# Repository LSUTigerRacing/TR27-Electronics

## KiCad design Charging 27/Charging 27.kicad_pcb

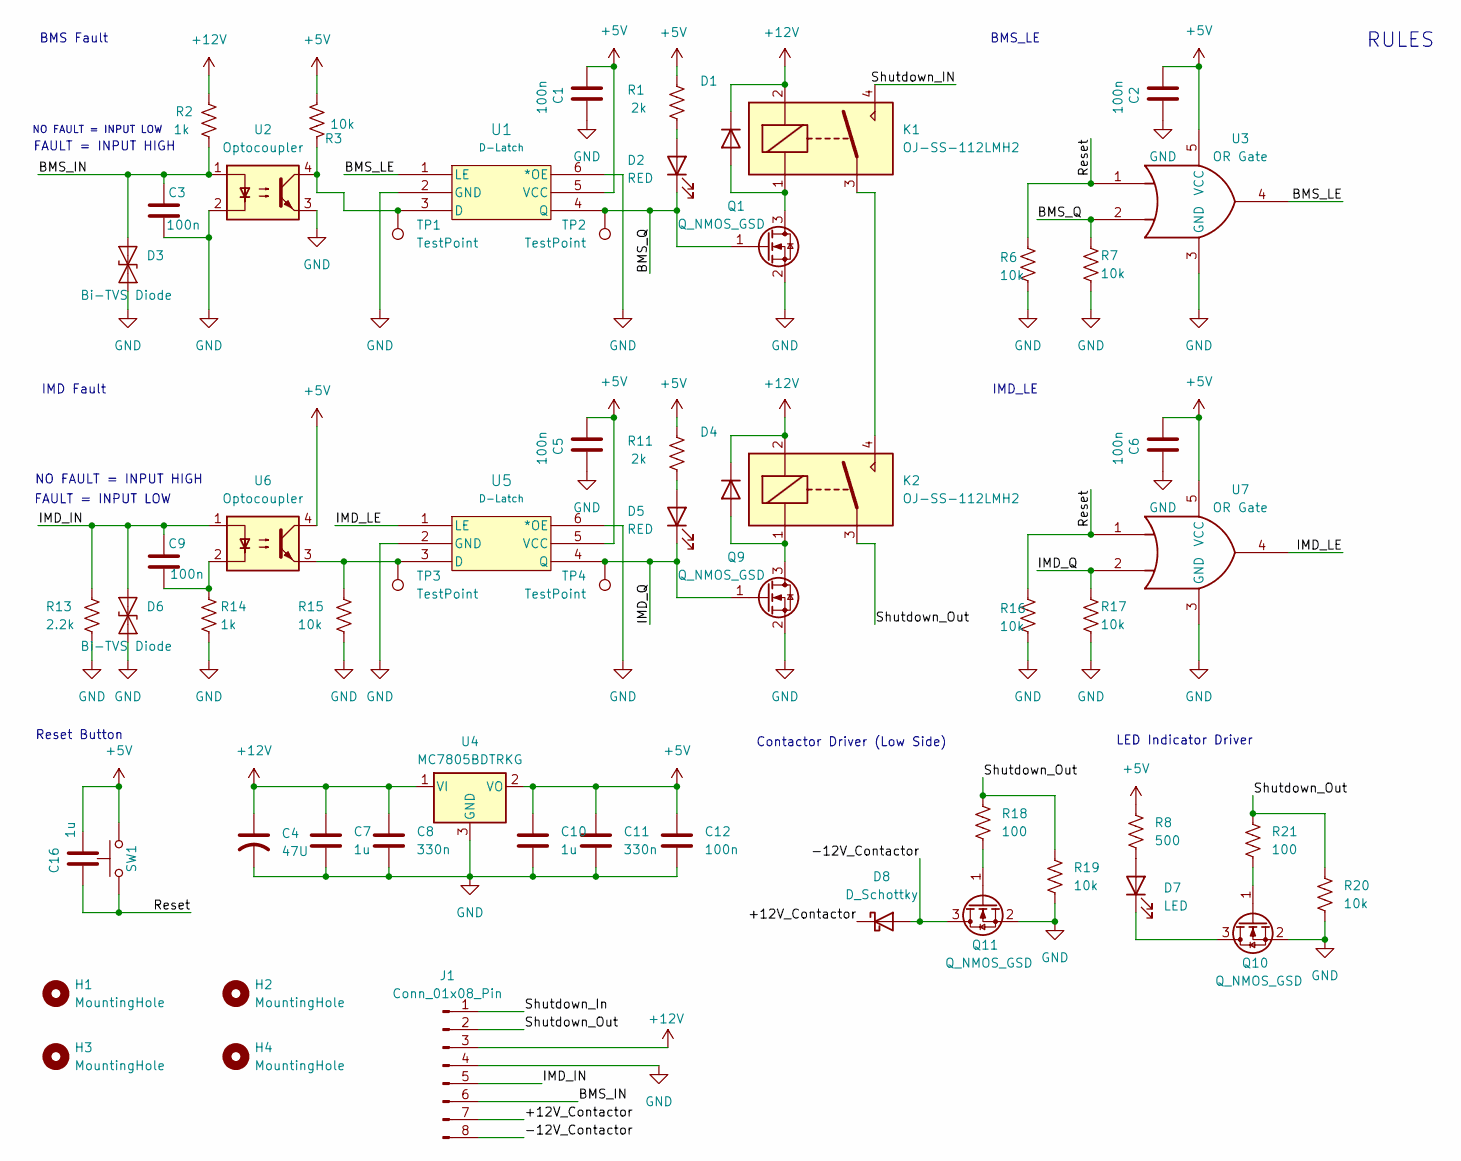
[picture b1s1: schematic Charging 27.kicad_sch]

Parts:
C1, C2, C5, C6: 100n; C_0603_1608Metric; Mouser# 603-AC0603KR9BB104; JLC# C1591
C3, C9: 100n; C_0603_1608Metric; Mouser# 603-AC0603KR9BB104; JLC# C133086
C4: 47U; CP_Elec_6.3x5.4; JLC# C2836440
C7, C10: 1u; C_0603_1608Metric; Mouser# 603-CC603KRX7R9BB105
C8, C11: 330n; C_0603_1608Metric; Mouser# 603-CC603KRX7R6BB334
C12: 100n; C_0603_1608Metric; Mouser# AC0603KRX7R9BB104
C16: 1u; C_0603_1608Metric; Mouser# 603-AC0603KR9BB104; JLC# C1591
D1, D4: D_SOD-323; Mouser# N/A; Digikey# 5399-1N4007WSCT-ND
D2, D5: RED; LED_0805_2012Metric_Pad1.15x1.40mm_HandSolder; Digikey# 475-LSR976-NR-1CT-ND
D3, D6: Bi-TVS Diode; D_SOD-523; Mouser# 750-CPDUR12V-HF; JLC# C2443698
D7: LED; D_1206_3216Metric_Pad1.42x1.75mm_HandSolder; MOUSER 645-598-8260-107F
D8: D_Schottky; D_SOD-323_HandSoldering; MOUSER 78-BAS170WS-HE3_A-08
H1, H2, H3, H4: MountingHole; MountingHole_3.2mm_M3_DIN965_Pad
J1: Conn_01x08_Pin; CONN_SD-43650-002_08_MOL
K1, K2: OJ-SS-112LMH2; OJSS112LMH2; Mouser# 655-OJ-SS-112LMH2
Q1, Q9, Q10, Q11: Q_NMOS_GSD; SOT-23; Mouser# 637-MMFTN6001; JLC# C151421
R1, R11: 2k; R_0805_2012Metric; Mouser# 603-RC0805FR-072KL; JLC# C137097
R2, R14: 1k; R_0805_2012Metric; JLC# C137088
R3, R6, R7, R15, R16, R17: 10k; R_0805_2012Metric; JLC# C137088
R8: 500; R_0603_1608Metric; Mouser# 603-RT0603BRC07500RL
R13: 2.2k; R_1206_3216Metric; Mouser# 660-SG73P2BTTD2201F; JLC# C137088
R18, R21: 100; R_0805_2012Metric; Mouser# 603-AA0805FR-13100RL
R19, R20: 10k; R_0805_2012Metric; Mouser# 603-RC1210JR-0710KL
SW1: SW_Omron_B3FS; SW_SPST_Omron_B3FS-100xP; Mouser# 653-B3FS-1000P; JLC# C271750
TP1, TP2, TP3, TP4: TestPoint; TestPoint_Pad_1.0x1.0mm
U1, U5: D-Latch; SOT-363_SC-70-6; Digikey# 296-18775-1-ND
U2, U6: Optocoupler; SSOP-4_VOS617A_VIS; Digikey# VOS617A-3TTR-ND
U3, U7: OR Gate; SOT-353_SC-70-5; Mouser# 595-SN74LVC1G32DCKR
U4: MC7805BDTRKG; TO-252-3_TabPin2

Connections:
+5V: C1.1, C2.1, C5.1, C6.1, C10.1, C11.1, C12.1, C16.1, R1.2, R3.1, R8.1, R11.2, SW1.2, U1.5 (VCC), U3.5 (VCC), U4.2 (VO), U5.5 (VCC), U6.4, U7.5 (VCC)
+12V: C4.1, C7.1, C8.1, D1.1 (K), D4.1 (K), J1.3, K1.2, K2.2, R2.2, U4.1 (VI)
/+12V_Contactor: D8.1 (K), J1.7
/-12V_Contactor: D8.2 (A), J1.8, Q11.3 (D)
/BMS_IN: C3.1, D3.2 (A2), J1.6, R2.1, U2.1
/BMS_LE: U1.1 (LE), U3.4
/BMS_Q: D2.1 (K), Q1.1 (G), R7.2, TP2.1 (1_1), U1.4 (Q), U3.2
/IMD_IN: C9.1, D6.2 (A2), J1.5, R13.2, U6.1
/IMD_LE: U5.1 (LE), U7.4
/IMD_Q: D5.1 (K), Q9.1 (G), R17.2, TP4.1 (1_1), U5.4 (Q), U7.2
/Reset: C16.2, R6.2, R16.2, SW1.1, U3.1, U7.1
/Shutdown_IN: K1.4
/Shutdown_In: J1.1
/Shutdown_Out: J1.2, K2.3, R18.1, R19.1, R20.1, R21.1
GND: C1.2, C2.2, C3.2, C4.2, C5.2, C6.2, C7.2, C8.2, C10.2, C11.2, C12.2, D3.1 (A1), D6.1 (A1), J1.4, Q1.2 (S), Q9.2 (S), Q10.2 (S), Q11.2 (S), R6.1, R7.1, R13.1, R14.1, R15.1, R16.1, R17.1, R19.2, R20.2, U1.2 (GND), U1.6 (*OE), U2.2, U2.3, U3.3 (GND), U4.3 (GND), U5.2 (GND), U5.6 (*OE), U7.3 (GND)
unnamed: C9.2, R14.2, U6.2
unnamed: D1.2 (A), K1.1, Q1.3 (D)
unnamed: D2.2 (A), R1.1
unnamed: D4.2 (A), K2.1, Q9.3 (D)
unnamed: D5.2 (A), R11.1
unnamed: D7.2 (A), R8.2
unnamed: D7.1 (K), Q10.3 (D)
unnamed: K1.3, K2.4
unnamed: Q10.1 (G), R21.2
unnamed: Q11.1 (G), R18.2
unnamed: R3.2, TP1.1 (1_1), U1.3 (D), U2.4
unnamed: R15.2, TP3.1 (1_1), U5.3 (D), U6.3

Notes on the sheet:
BMS Fault
IMD_LE
Reset Button
Contactor Driver (Low Side)
LED Indicator Driver
NO FAULT = INPUT LOW
BMS_LE
FAULT = INPUT LOW
NO FAULT = INPUT HIGH
IMD Fault
RULES
FAULT = INPUT HIGH

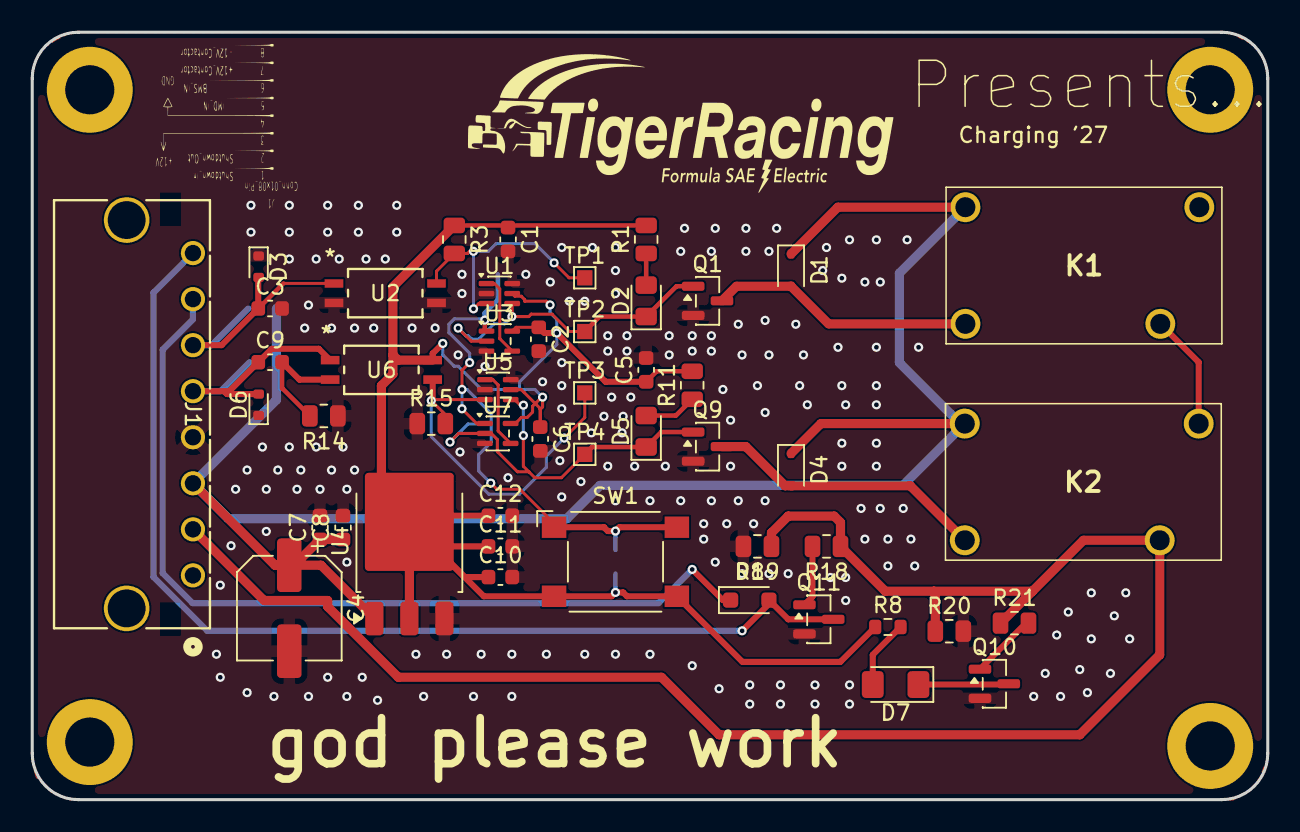
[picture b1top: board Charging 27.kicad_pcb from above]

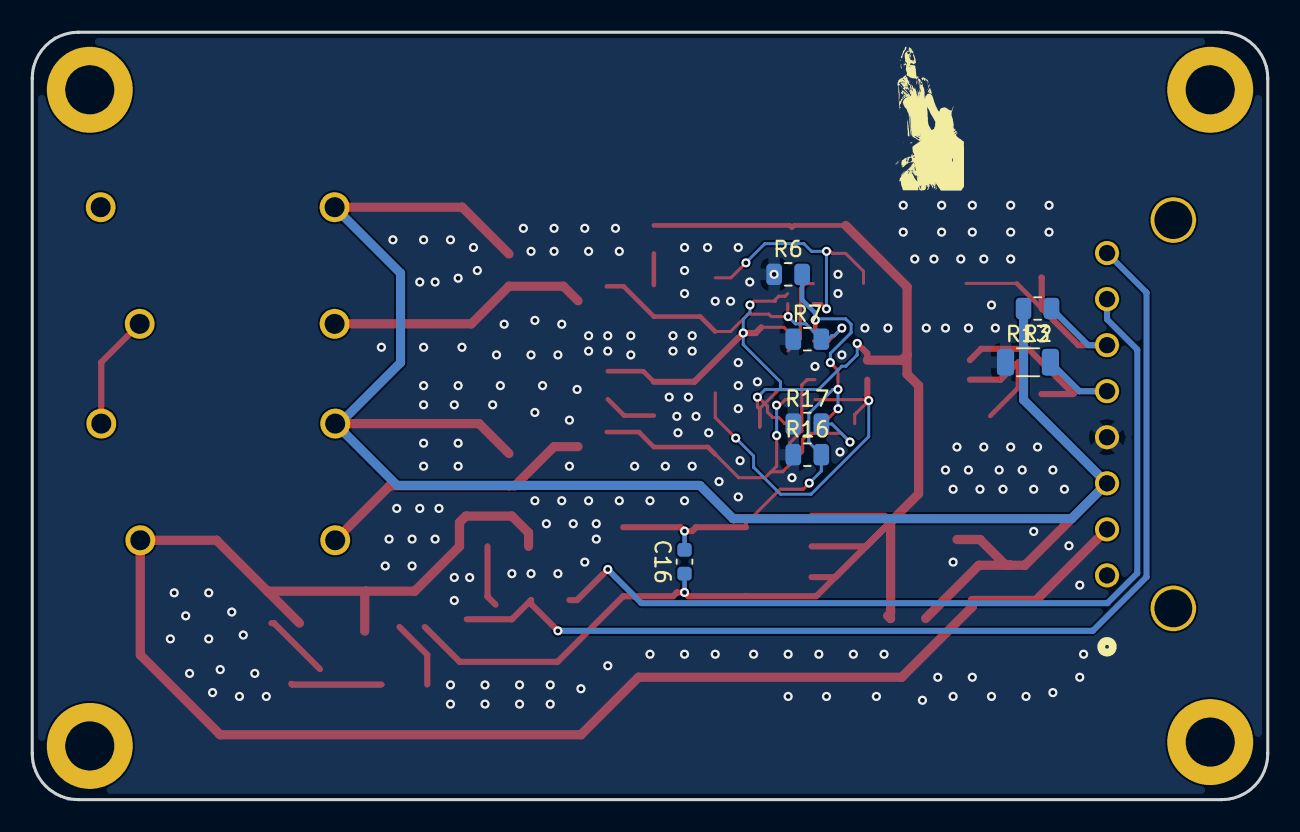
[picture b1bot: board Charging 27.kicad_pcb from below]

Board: 2 copper layers, 80.5 x 50.0 mm, 60 parts (7 on the bottom side), 25 nets.

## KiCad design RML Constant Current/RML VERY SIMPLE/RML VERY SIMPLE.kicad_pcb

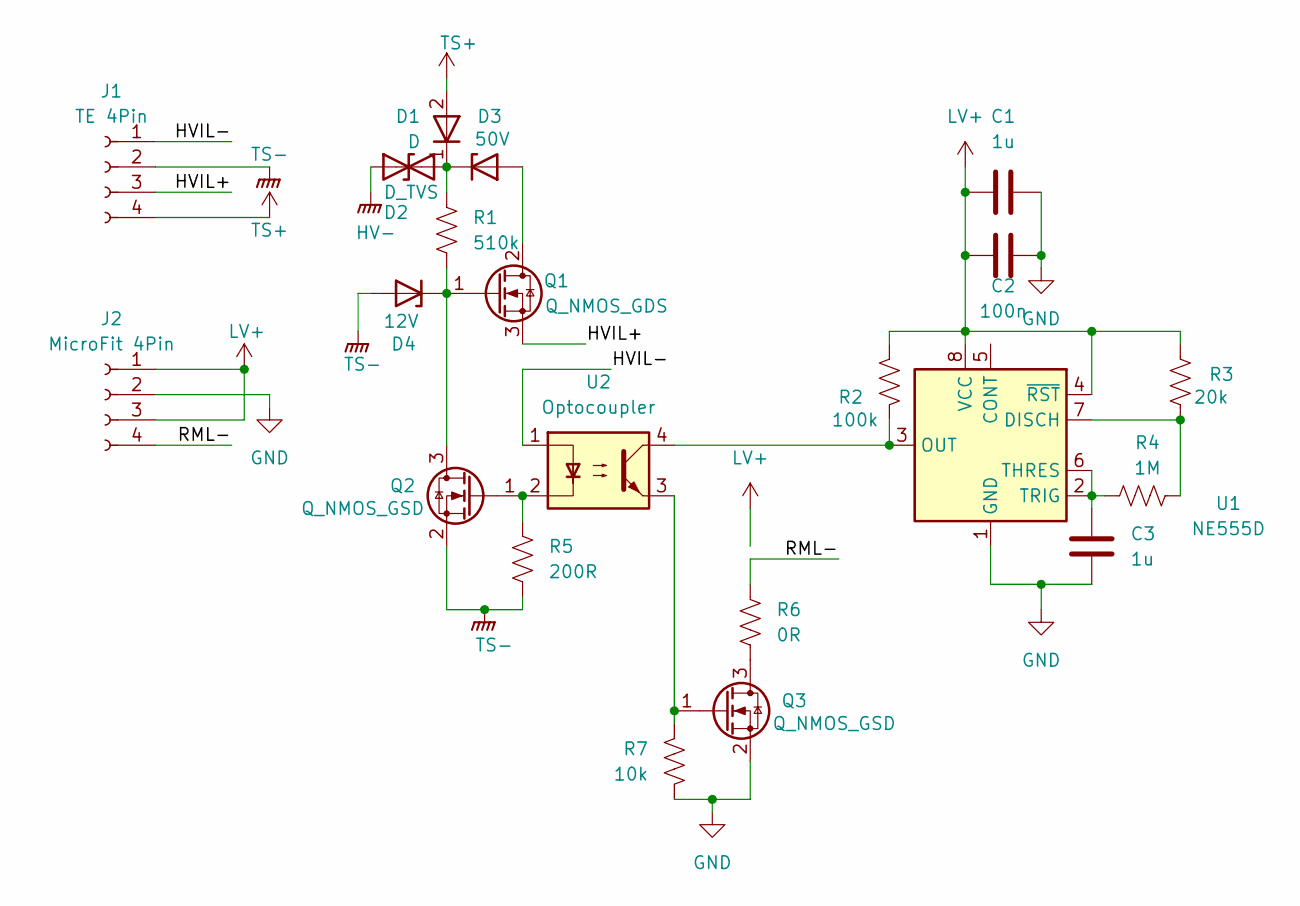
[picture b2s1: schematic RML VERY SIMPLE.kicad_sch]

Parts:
C1, C3: 1u; C_0805_2012Metric; Mouser# 603-AC0805KKX7R9B105; Digikey# 13-AC0805KKX7R9BB105CT-ND
C2: 100n; C_0603_1608Metric; Mouser# 603-AC0603KR9BB104; Digikey# 311-3034-2-ND
D1: D; D_SMA; Mouser# 637-M7
D2: D_TVS; D_SMA; Mouser# 652-SMAJ350CA; Digikey# SMAJ350CALFCT-ND
D3: 50V; D_SOD-123F; Mouser# 771-HPZR-C50X; Digikey# 1727-HPZR-C50XCT-ND
D4: 12V; D_SOD-123F; Mouser# 637-MMSZ5242B; Digikey# 4878-MMSZ5242BCT-ND
J1: TE 4Pin; 214450884; Mouser# 571-2-1445088-4; Digikey# A144905-ND
J2: MicroFit 4Pin; CONN_SD-43045-001_04_MOL_Microfit; Mouser# 538-43045-0400; Digikey# WM1814-ND
Q1: Q_NMOS_GDS; TO-220-3_Horizontal_TabUp; Mouser# 747-IXTP08N50D2; Digikey# 238-IXTP08N50D2-ND
Q2, Q3: Q_NMOS_GSD; SOT-23; Mouser# 637-MMFTN6001; JLC# C151421
R1: 510k; R_1206_3216Metric; Mouser# 667-ERJ-P08J514V; Digikey# P510KALCT-ND
R2: 100k; R_0805_2012Metric; Mouser# 603-RC0805FR-10100KL; Digikey# 13-RC0805FR-10100KLCT-ND
R3: 20k; R_0805_2012Metric; Mouser# 603-AC0805FR-0720KL; Digikey# YAG3708CT-ND
R4: 1M; R_0805_2012Metric; Mouser# 603-RC0805FR-071MP
R5: 200R; R_0805_2012Metric; Mouser# 603-AC0805FR-13200RL
R6: 0R; R_0805_2012Metric; Mouser# 603-RC0805JR-070RL
R7: 10k; R_0805_2012Metric; Mouser# 603-RC0805FR-0710KL
U1: NE555D; SOIC-8_3.9x4.9mm_P1.27mm; Mouser# 595-NE555DR; Digikey# 296-6501-1-ND
U2: Optocoupler; Q_Wurth_WL-OCPT_LSOP4-STANDARD; Mouser# 78-VOLA617A-3X001T

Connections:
/HVIL+: J1.3, Q1.3 (S)
/HVIL-: J1.1, U2.1
/RML-: J2.4, R6.1
GND: C1.2, C2.2, C3.2, J2.2, Q3.2 (S), R7.2, U1.1 (GND)
HV-: D2.1 (A1)
LV+: C1.1, C2.1, J2.1, J2.3, R2.1, R3.1, U1.4 (~RST), U1.8 (VCC)
unnamed: D1.1 (K), D2.2 (A2), D3.1 (K), R1.1
unnamed: D3.2 (A), Q1.2 (D)
unnamed: D4.1 (K), Q1.1 (G), Q2.3 (D), R1.2
unnamed: Q2.1 (G), R5.1, U2.2
unnamed: Q3.3 (D), R6.2
unnamed: Q3.1 (G), R7.1, U2.3
unnamed: R3.2, R4.1, U1.7 (DISCH)
unnamed: R2.2, U1.3 (OUT), U2.4
unnamed: C3.1, R4.2, U1.2 (TRIG), U1.6 (THRES)
TS+: D1.2 (A), J1.4
TS-: D4.2 (A), J1.2, Q2.2 (S), R5.2

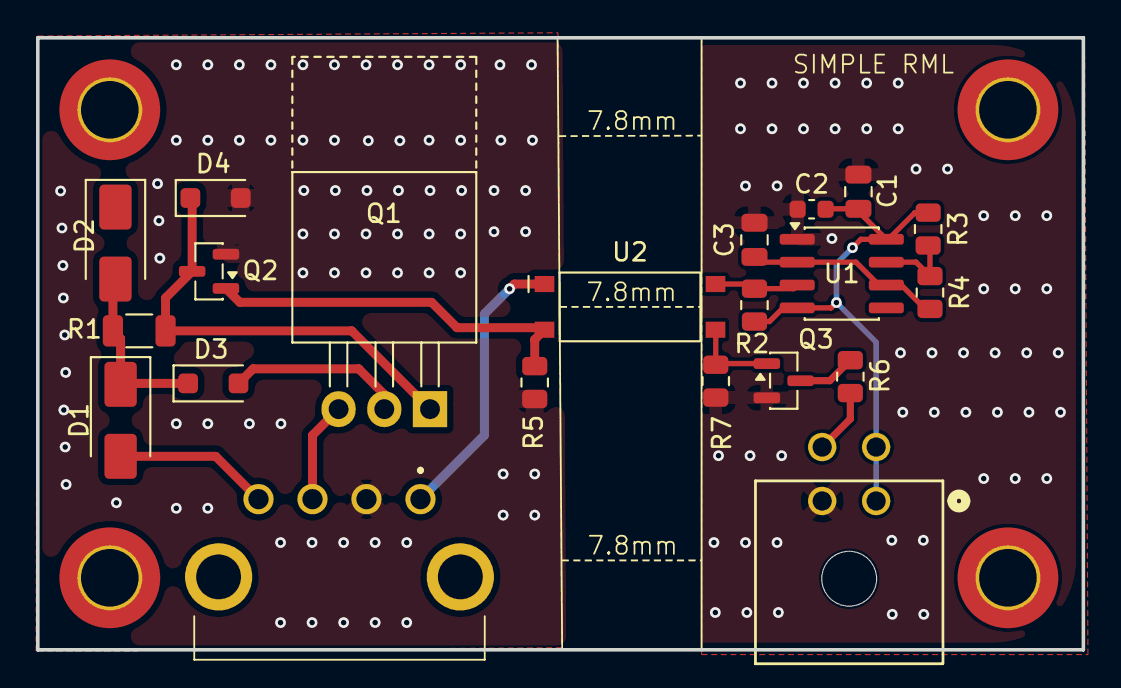
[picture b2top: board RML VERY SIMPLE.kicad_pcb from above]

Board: 2 copper layers, 58.1 x 34.0 mm, 25 parts (0 on the bottom side), 16 nets.

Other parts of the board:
H1, H2, H3, H4: MountingHole; MountingHole_3.2mm_M3_DIN965_Pad_TopOnly

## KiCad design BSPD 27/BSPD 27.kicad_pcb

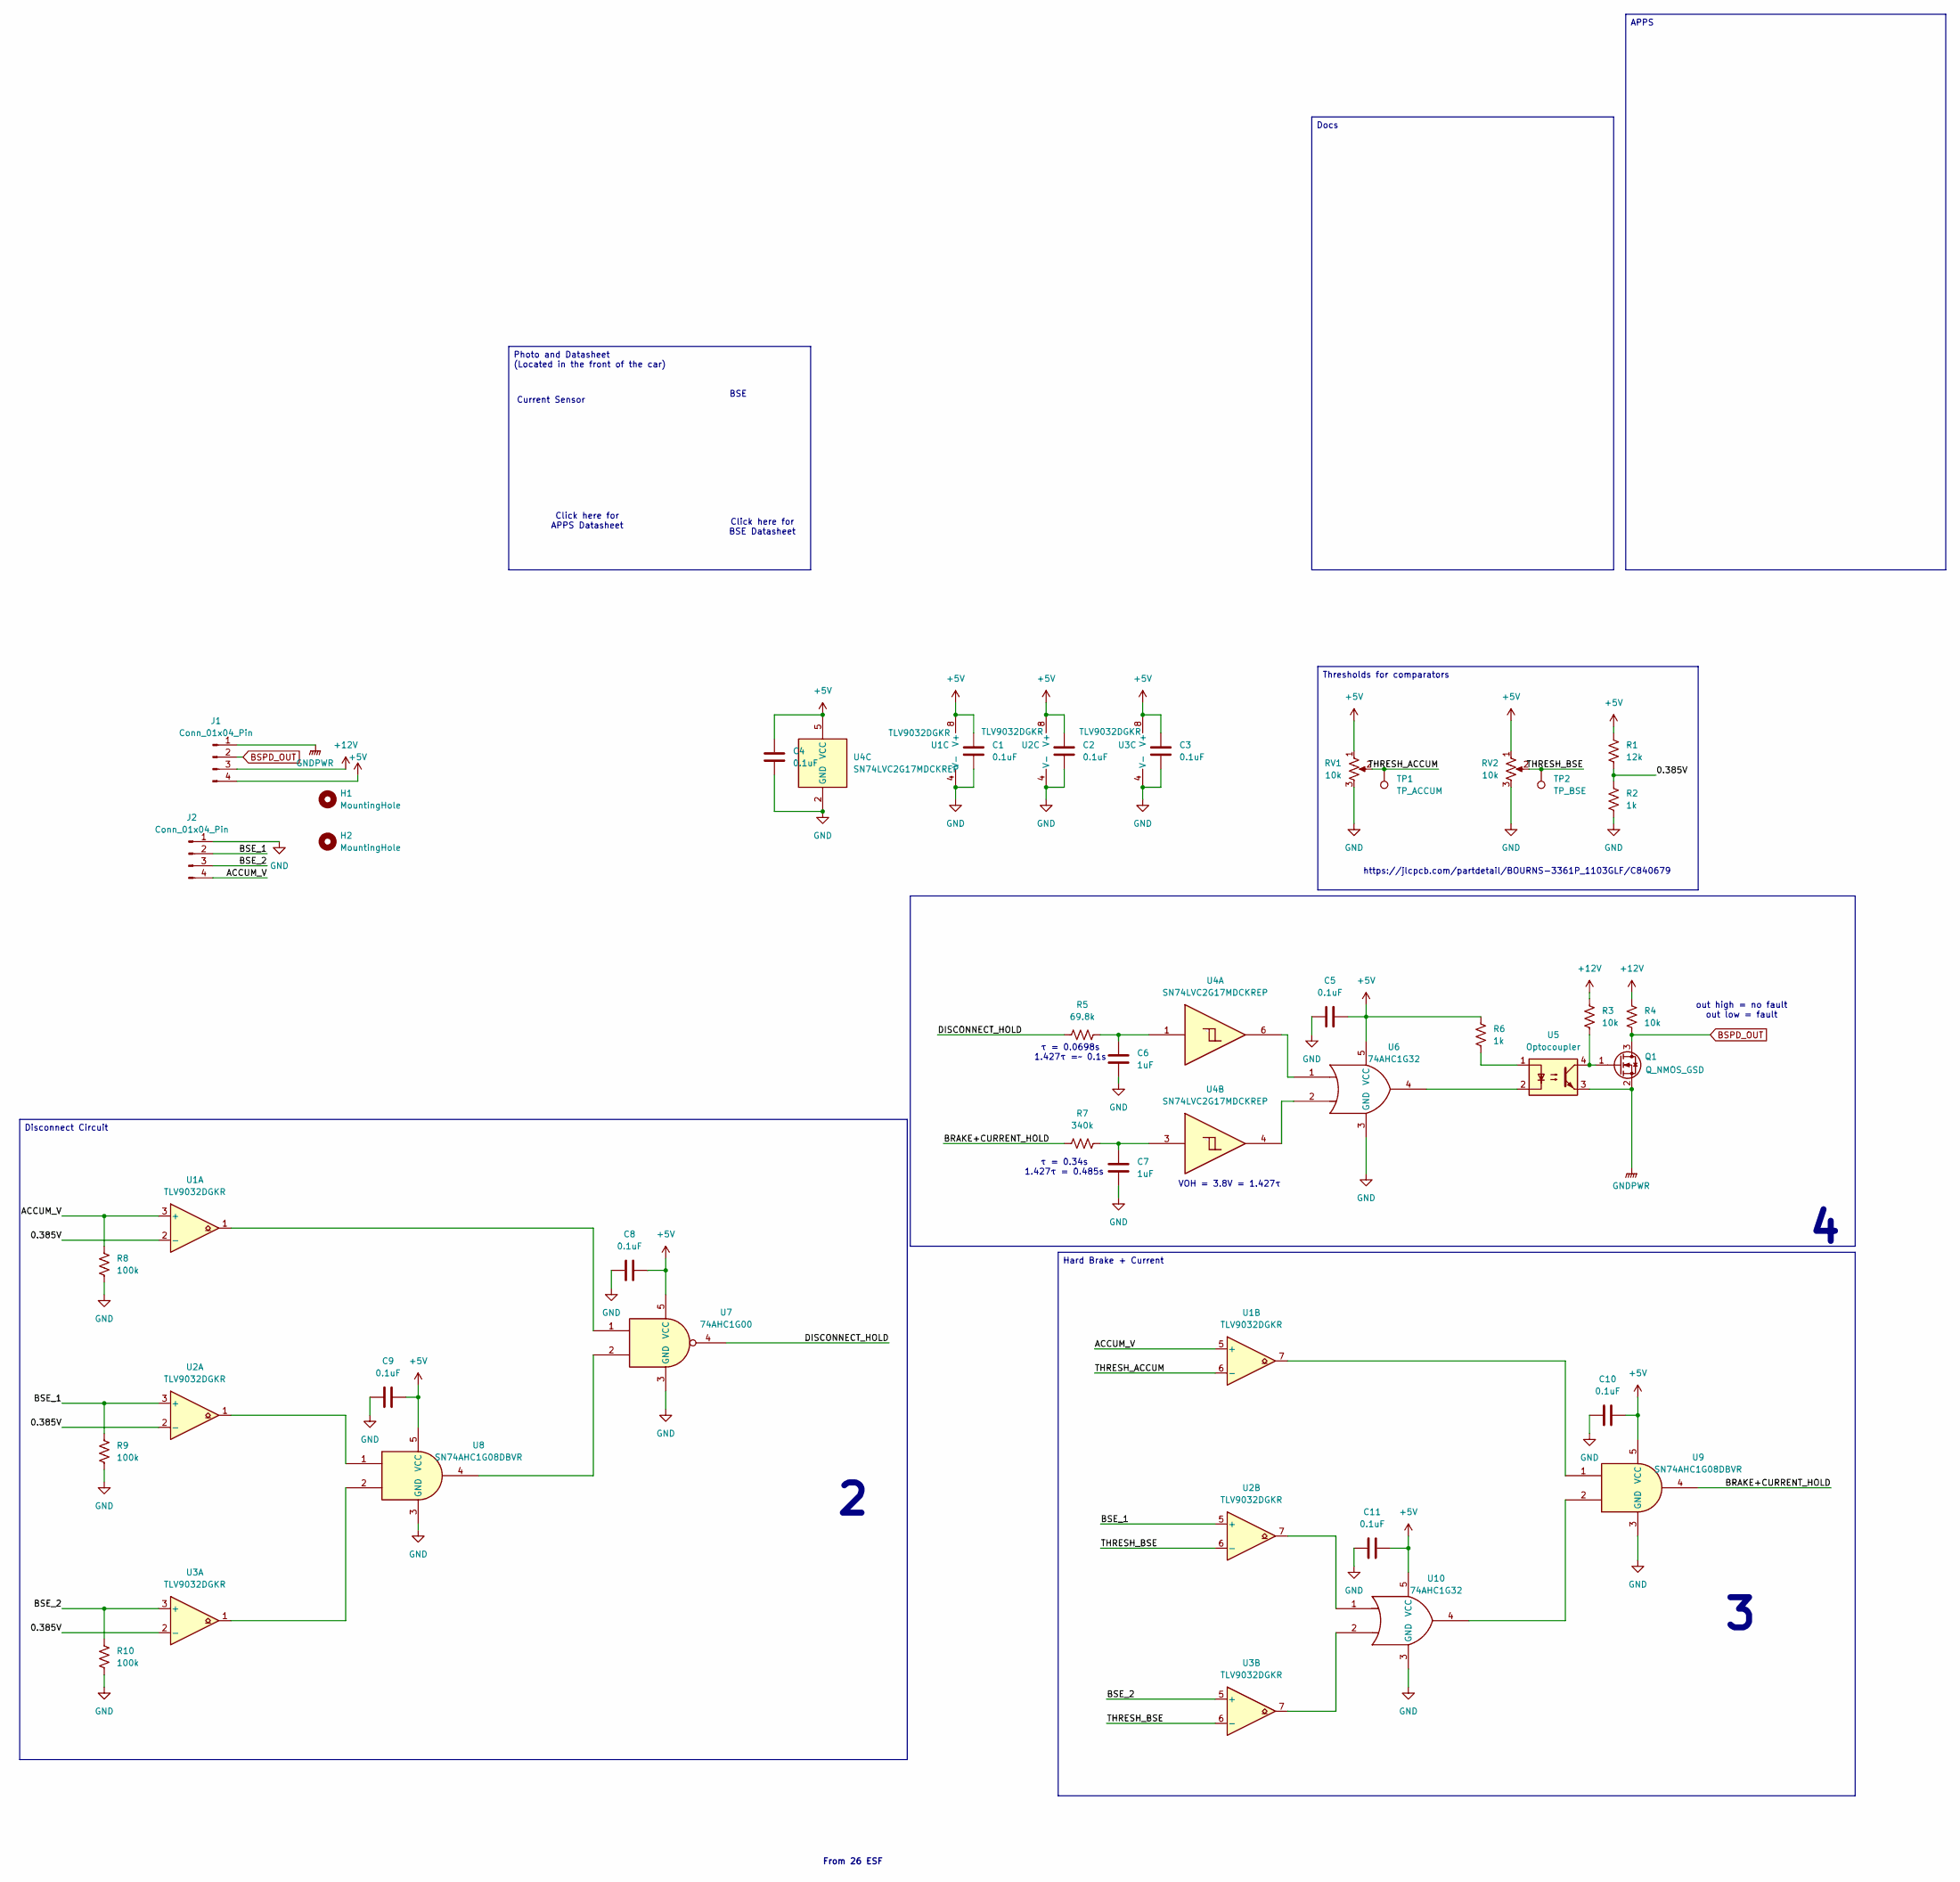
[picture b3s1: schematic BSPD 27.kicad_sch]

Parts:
C1, C2, C3, C4, C5, C8, C9, C10, C11: 0.1uF; C_0603_1608Metric; Mouser# AC0603KRX7R9BB104; JLC# C24497
C6, C7: 1uF; C_0805_2012Metric; Mouser# AC0805KKX7R9BB105; JLC# C782156
H1, H2: MountingHole; MountingHole_3.2mm_M3_DIN965_Pad
J1, J2: Conn_01x04_Pin; SAMTEC_TSW-104-07-L-S; Mouser# N/A; Digikey# N/A
Q1: Q_NMOS_GSD; SOT-23; Mouser# 637-MMFTN6001; JLC# C151421
R1: 12k; R_0805_2012Metric; JLC# C182355
R2: 1k; R_0805_2012Metric; JLC# C230096
R3, R4: 10k; R_0805_2012Metric; JLC# C17414
R5: 69.8k; R_0805_2012Metric; JLC# C230096
R6: 1k; R_0805_2012Metric; Digikey# 311-1.00KCRCT-ND
R7: 340k; R_0805_2012Metric; JLC# C3000590
R8, R9, R10: 100k; R_0805_2012Metric; JLC# C185765
RV1, RV2: 10k; PVG5A103C03B00; Mouser# 81-PVG5A103C03B00; JLC# C48731759
TP1: TP_ACCUM; TestPoint_Pad_D1.5mm
TP2: TP_BSE; TestPoint_Pad_D1.5mm
U1, U2, U3: TLV9032DGKR; SOP65P490X110-8N; Digikey# 296-TLV9032DGKRCT-ND
U4: SN74LVC2G17MDCKREP; SOT-363_SC-70-6; Digikey# 296-22358-1-ND
U5: Optocoupler; SSOP-4_VOS617A_VIS; Digikey# 78-VOS617A-3T
U6, U10: 74AHC1G32; SOT-353_SC-70-5; Mouser# 595-SN74LVC1G32DCKR
U7: 74AHC1G00; SOT-353_SC-70-5; Mouser# 595-SN74LVC1G00DCKR
U8: SN74AHC1G08DBVR; SOT-353_SC-70-5; Mouser# 595-SN74LVC1G08DCKR; JLC# C7467
U9: SN74AHC1G08DBVR; SOT-353_SC-70-5; Mouser# 595-SN74LVC1G11DCKR; JLC# C7467

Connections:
+5V: C1.1, C2.1, C3.1, C4.2, C5.2, C8.2, C9.2, C10.2, C11.2, J1.4, R1.2, R6.1, RV1.1, RV2.1, U1.8 (V+), U2.8 (V+), U3.8 (V+), U4.5 (VCC), U6.5 (VCC), U7.5 (VCC), U8.5 (VCC), U9.5 (VCC), U10.5 (VCC)
+12V: J1.3, R3.1, R4.1
/0.385V: R1.1, R2.2, U1.2 (-), U2.2 (-), U3.2 (-)
/ACCUM_V: J2.4, R8.2, U1.3 (+), U1.5 (+)
/BRAKE+CURRENT_HOLD: R7.1, U9.4
/BSE_1: J2.2, R9.2, U2.3 (+), U2.5 (+)
/BSE_2: J2.3, R10.2, U3.3 (+), U3.5 (+)
/DISCONNECT_HOLD: R5.1, U7.4
/THRESH_ACCUM: RV1.2, TP1.1 (1_1), U1.6 (-)
/THRESH_BSE: RV2.2, TP2.1 (1_1), U2.6 (-), U3.6 (-)
BSPD_OUT: J1.2, Q1.3 (D), R4.2
GND: C1.2, C2.2, C3.2, C4.1, C5.1, C6.2, C7.2, C8.1, C9.1, C10.1, C11.1, J2.1, R2.1, R8.1, R9.1, R10.1, RV1.3, RV2.3, U1.4 (V-), U2.4 (V-), U3.4 (V-), U4.2 (GND), U6.3 (GND), U7.3 (GND), U8.3 (GND), U9.3 (GND), U10.3 (GND)
GNDPWR: J1.1, Q1.2 (S), U5.3
unnamed: C6.1, R5.2, U4.1
unnamed: C7.1, R7.2, U4.3
unnamed: Q1.1 (G), R3.2, U5.4
unnamed: R6.2, U5.1
unnamed: U1.1, U7.1
unnamed: U1.7, U9.1
unnamed: U2.1, U8.1
unnamed: U3.1, U8.2
unnamed: U4.4, U6.2
unnamed: U4.6, U6.1
unnamed: U5.2, U6.4
unnamed: U7.2, U8.4
unnamed: U2.7, U10.1
unnamed: U3.7, U10.2
unnamed: U9.2, U10.4

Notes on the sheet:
Current Sensor
Click here for BSE Datasheet
τ = 0.34s 1.427τ = 0.485s
τ = 0.0698s 1.427τ =~ 0.1s
BSE
out high = no fault out low = fault
VOH = 3.8V = 1.427τ
From 26 ESF
Click here for APPS Datasheet
https://jlcpcb.com/partdetail/BOURNS-3361P_1103GLF/C840679
Hard Brake + Current
Thresholds for comparators
Disconnect Circuit
APPS
Photo and Datasheet (Located in the front of the car)
Docs

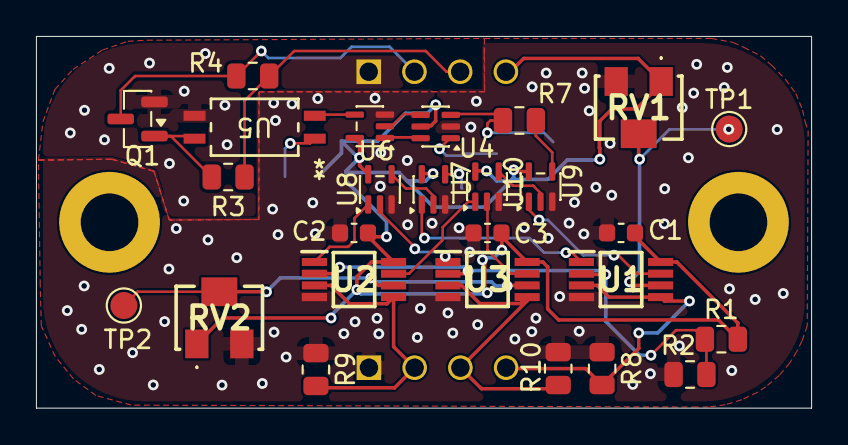
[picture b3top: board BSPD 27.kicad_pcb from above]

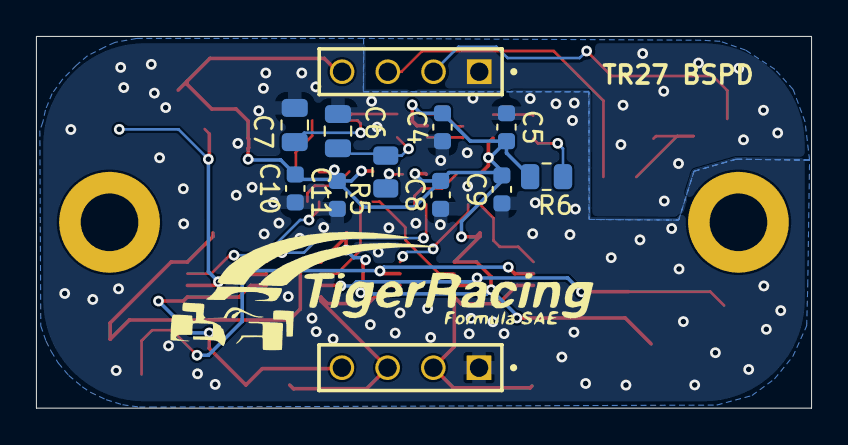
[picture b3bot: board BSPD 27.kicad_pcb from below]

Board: 2 copper layers, 43.1 x 20.7 mm, 40 parts (12 on the bottom side), 28 nets.

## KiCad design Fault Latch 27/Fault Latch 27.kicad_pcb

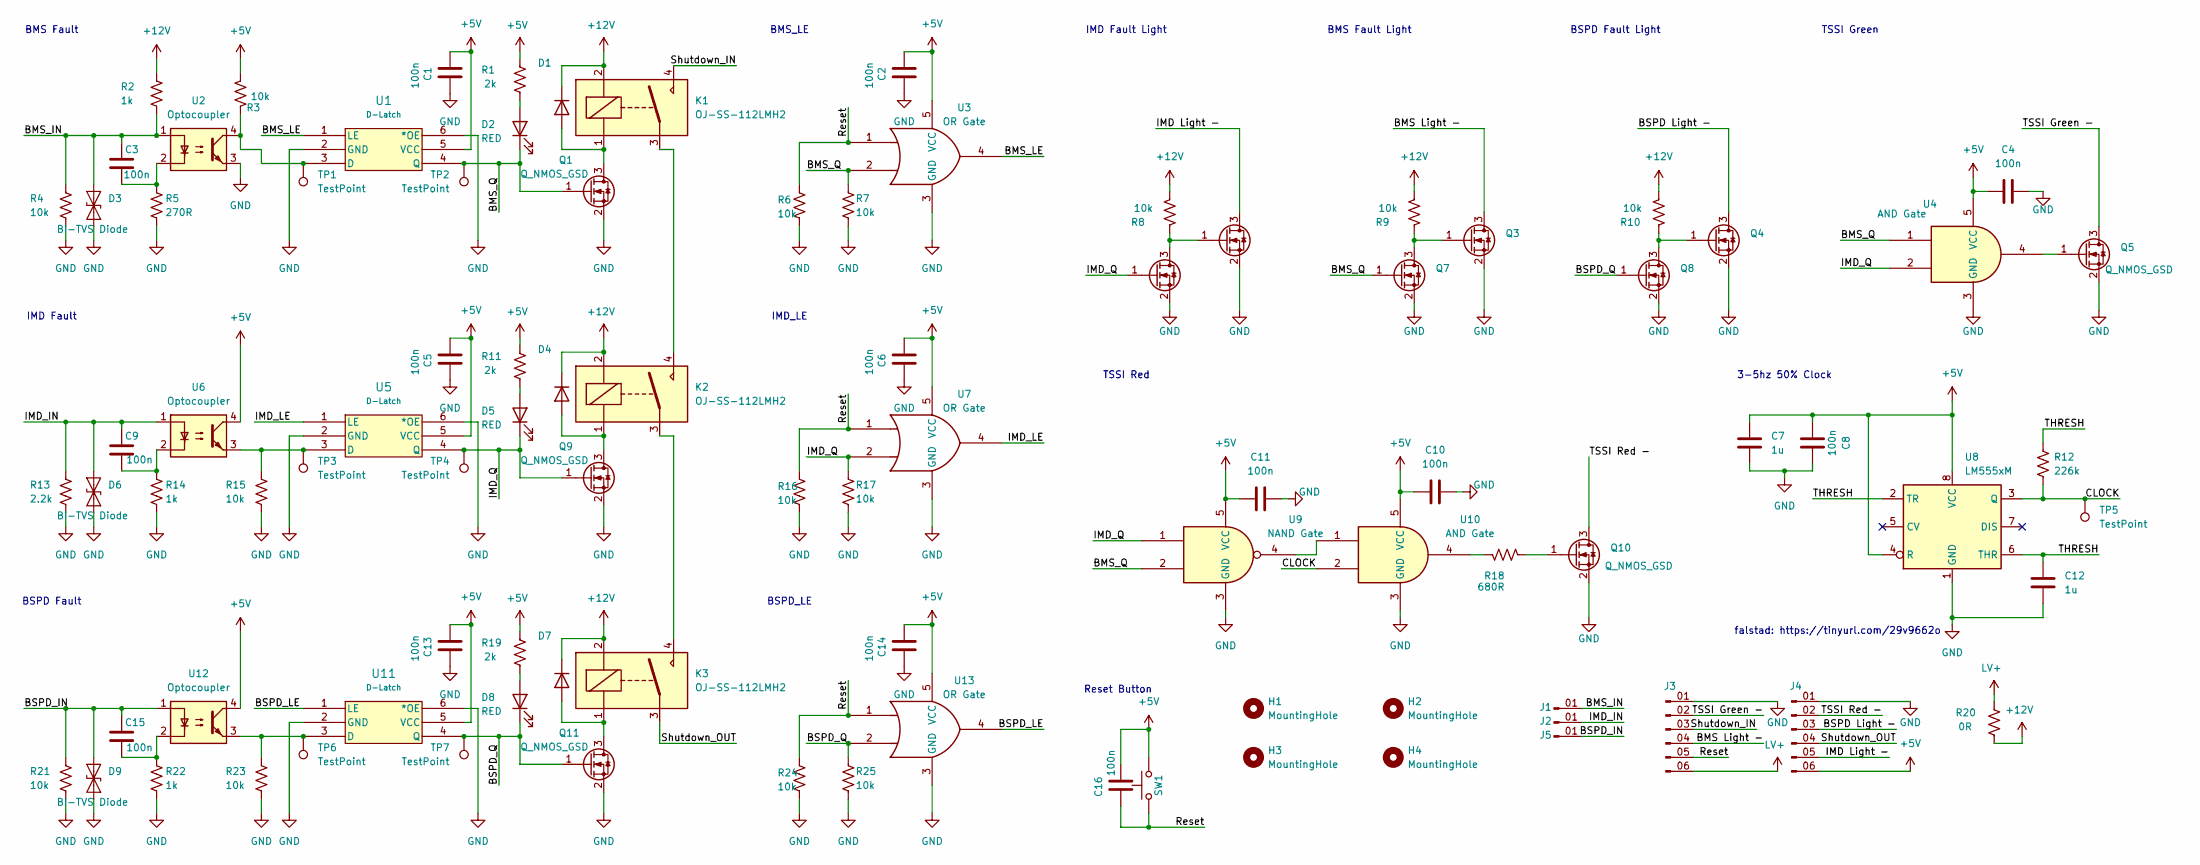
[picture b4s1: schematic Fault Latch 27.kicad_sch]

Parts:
C1, C2, C5, C6, C13, C14, C16: 100n; C_0603_1608Metric; Mouser# 603-AC0603KR9BB104; JLC# C1591
C3, C4, C9, C10, C11, C15: 100n; C_0603_1608Metric; Mouser# 603-AC0603KR9BB104; JLC# C133086
C7, C12: 1u; C_0805_2012Metric; Mouser# 603-AC0805KKX7R9B105; JLC# C1592
C8: 100n; C_0603_1608Metric; Mouser# 603-AC0603KR9BB104; JLC# C1590
D1, D4, D7: D_SOD-323; Mouser# N/A; Digikey# 5399-1N4007WSCT-ND
D2, D5, D8: RED; LED_0805_2012Metric_Pad1.15x1.40mm_HandSolder; Digikey# 475-LSR976-NR-1CT-ND
D3, D6, D9: Bi-TVS Diode; D_SOD-523; Mouser# 750-CPDUR12V-HF; JLC# C2443698
H1, H2, H3, H4: MountingHole; MountingHole_3.2mm_M3_DIN965_Pad
J1, J2, J5: Conn_01x01_Pin; SAMTEC_TSW-101-07-L-S
J3, J4: Conn_01x06_Pin; SAMTEC_TSW-103-07-L-D
K1, K2, K3: OJ-SS-112LMH2; OJSS112LMH2; Mouser# 655-OJ-SS-112LMH2
Q1, Q2, Q3, Q4, Q5, Q6, Q7, Q8, Q9, Q10, Q11: Q_NMOS_GSD; SOT-23; Mouser# 637-MMFTN6001; JLC# C151421
R1, R11, R19: 2k; R_0805_2012Metric; Mouser# 603-RC0805FR-072KL; JLC# C137097
R2, R14, R22: 1k; R_0805_2012Metric; JLC# C137088
R3, R4, R6, R7, R8, R9, R10, R15, R16, R17, R21, R23, R24, R25: 10k; R_0805_2012Metric; JLC# C137088
R5: 270R; R_0805_2012Metric
R12: 226k; R_0805_2012Metric; Mouser# 603-RC0805FR-07226KL; JLC# C17900
R13: 2.2k; R_1206_3216Metric; Mouser# 660-SG73P2BTTD2201F; JLC# C137088
R18: 680R; R_0805_2012Metric; Mouser# 603-RC0805FR-07680RL; JLC# C137071
R20: 0R; R_0805_2012Metric; Digikey# 311-0.0ARCT-ND
SW1: SW_Omron_B3FS; SW_SPST_Omron_B3FS-100xP; Mouser# 653-B3FS-1000P; JLC# C271750
TP1, TP2, TP3, TP4, TP5, TP6, TP7: TestPoint; TestPoint_Pad_1.0x1.0mm
U1, U5, U11: D-Latch; SOT-363_SC-70-6; Digikey# 296-18775-1-ND
U2, U6, U12: Optocoupler; SSOP-4_VOS617A_VIS; Digikey# VOS617A-3TTR-ND
U3, U7, U13: OR Gate; SOT-353_SC-70-5; Mouser# 595-SN74LVC1G32DCKR
U4, U10: AND Gate; SOT-353_SC-70-5; Mouser# 595-SN74LVC1G11DCKR; JLC# C7467
U8: LM555xM; SOIC-8_3.9x4.9mm_P1.27mm; Mouser# 926-LMC555CMX/NOPB; JLC# C90760
U9: NAND Gate; SOT-353_SC-70-5; Mouser# 595-SN74LVC1G00DCKR

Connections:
+5V: C1.1, C2.1, C4.2, C5.1, C6.1, C7.1, C8.1, C10.2, C11.2, C13.1, C14.1, C16.1, J4.06 (Pin_6), R1.2, R3.1, R11.2, R19.2, SW1.2, U1.5 (VCC), U3.5 (VCC), U4.5 (VCC), U5.5 (VCC), U6.4, U7.5 (VCC), U8.4 (R), U8.8 (VCC), U9.5 (VCC), U10.5 (VCC), U11.5 (VCC), U12.4, U13.5 (VCC)
+12V: D1.1 (K), D4.1 (K), D7.1 (K), K1.2, K2.2, K3.2, R2.2, R8.1, R9.1, R10.1, R20.1
/BMS Light -: J3.04 (Pin_4), Q3.3 (D)
/BMS_IN: C3.1, D3.2 (A2), J1.01 (Pin_1_01), R2.1, R4.2, U2.1
/BMS_LE: U1.1 (LE), U3.4
/BMS_Q: D2.1 (K), Q1.1 (G), Q7.1 (G), R7.2, TP2.1 (1_1), U1.4 (Q), U3.2, U4.1, U9.2
/BSPD Light -: J4.03 (Pin_3), Q4.3 (D)
/BSPD_IN: C15.1, D9.2 (A2), J5.01 (Pin_1_01), R21.2, U12.1
/BSPD_LE: U11.1 (LE), U13.4
/BSPD_Q: D8.1 (K), Q8.1 (G), Q11.1 (G), R25.2, TP7.1 (1_1), U11.4 (Q), U13.2
/CLOCK: R12.2, TP5.1 (1_1), U8.3 (Q), U10.2
/IMD Light -: J4.05 (Pin_5), Q2.3 (D)
/IMD_IN: C9.1, D6.2 (A2), J2.01 (Pin_1_01), R13.2, U6.1
/IMD_LE: U5.1 (LE), U7.4
/IMD_Q: D5.1 (K), Q6.1 (G), Q9.1 (G), R17.2, TP4.1 (1_1), U4.2, U5.4 (Q), U7.2, U9.1
/Reset: C16.2, J3.05 (Pin_5), R6.2, R16.2, R24.2, SW1.1, U3.1, U7.1, U13.1
/Shutdown_IN: J3.03 (Pin_3), K1.4
/Shutdown_OUT: J4.04 (Pin_4), K3.3
/THRESH: C12.1, R12.1, U8.2 (TR), U8.6 (THR)
/TSSI Green -: J3.02 (Pin_2), Q5.3 (D)
/TSSI Red -: J4.02 (Pin_2), Q10.3 (D)
GND: C1.2, C2.2, C4.1, C5.2, C6.2, C7.2, C8.2, C10.1, C11.1, C12.2, C13.2, C14.2, D3.1 (A1), D6.1 (A1), D9.1 (A1), J3.01 (Pin_1), J4.01 (Pin_1), Q1.2 (S), Q2.2 (S), Q3.2 (S), Q4.2 (S), Q5.2 (S), Q6.2 (S), Q7.2 (S), Q8.2 (S), Q9.2 (S), Q10.2 (S), Q11.2 (S), R4.1, R5.1, R6.1, R7.1, R13.1, R14.1, R15.1, R16.1, R17.1, R21.1, R22.1, R23.1, R24.1, R25.1, U1.2 (GND), U1.6 (*OE), U2.3, U3.3 (GND), U4.3 (GND), U5.2 (GND), U5.6 (*OE), U7.3 (GND), U8.1 (GND), U9.3 (GND), U10.3 (GND), U11.2 (GND), U11.6 (*OE), U13.3 (GND)
LV+: J3.06 (Pin_6), R20.2
unnamed: C3.2, R5.2, U2.2
unnamed: C9.2, R14.2, U6.2
unnamed: C15.2, R22.2, U12.2
unnamed: D1.2 (A), K1.1, Q1.3 (D)
unnamed: D2.2 (A), R1.1
unnamed: D4.2 (A), K2.1, Q9.3 (D)
unnamed: D5.2 (A), R11.1
unnamed: D7.2 (A), K3.1, Q11.3 (D)
unnamed: D8.2 (A), R19.1
unnamed: K1.3, K2.4
unnamed: K2.3, K3.4
unnamed: Q2.1 (G), Q6.3 (D), R8.2
unnamed: Q3.1 (G), Q7.3 (D), R9.2
unnamed: Q4.1 (G), Q8.3 (D), R10.2
unnamed: Q5.1 (G), U4.4
unnamed: Q10.1 (G), R18.1
unnamed: R18.2, U10.4
unnamed: R3.2, TP1.1 (1_1), U1.3 (D), U2.4
unnamed: R15.2, TP3.1 (1_1), U5.3 (D), U6.3
unnamed: U9.4, U10.1
unnamed: R23.2, TP6.1 (1_1), U11.3 (D), U12.3

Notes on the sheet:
IMD Fault
BSPD Fault Light
TSSI Red
BMS Fault
Reset Button
falstad: https://tinyurl.com/29v9662o
BSPD_LE
TSSI Green
IMD Fault Light
3-5hz 50% Clock
BMS_LE
BSPD Fault
BMS Fault Light
IMD_LE

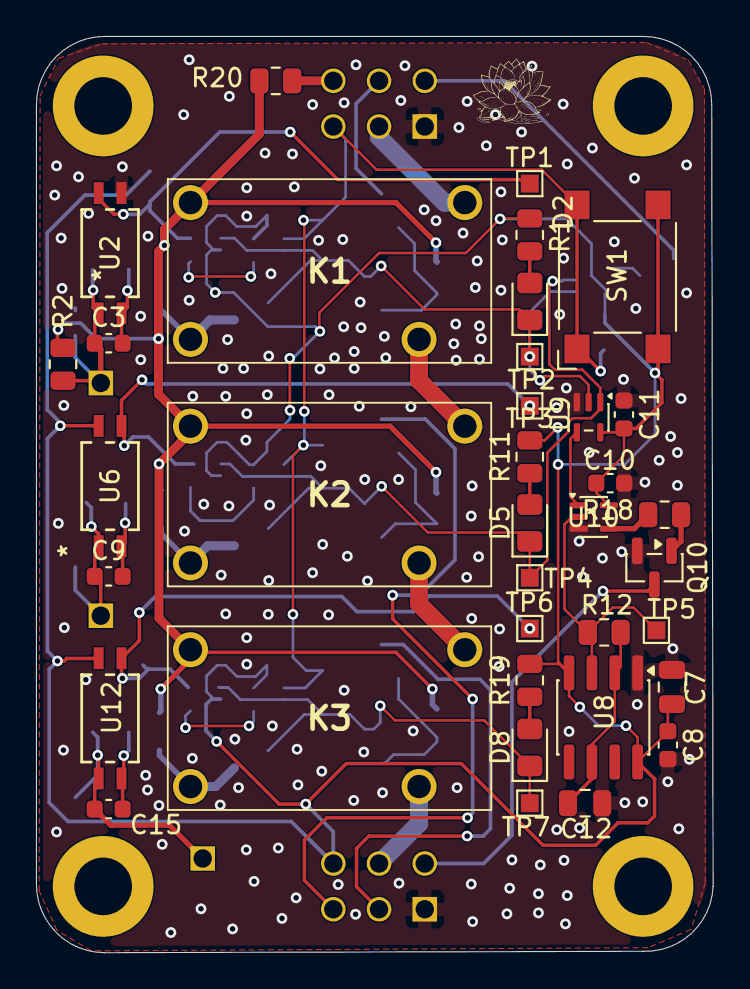
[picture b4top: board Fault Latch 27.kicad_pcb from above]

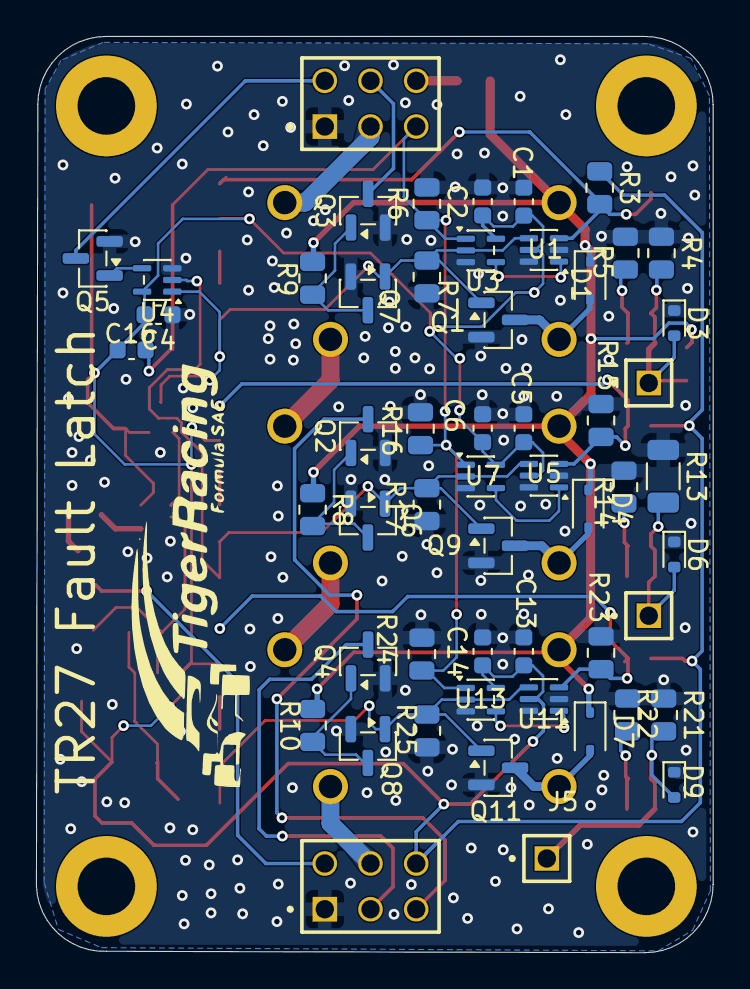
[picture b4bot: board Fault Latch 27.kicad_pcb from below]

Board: 2 copper layers, 37.6 x 50.9 mm, 94 parts (54 on the bottom side), 44 nets.
